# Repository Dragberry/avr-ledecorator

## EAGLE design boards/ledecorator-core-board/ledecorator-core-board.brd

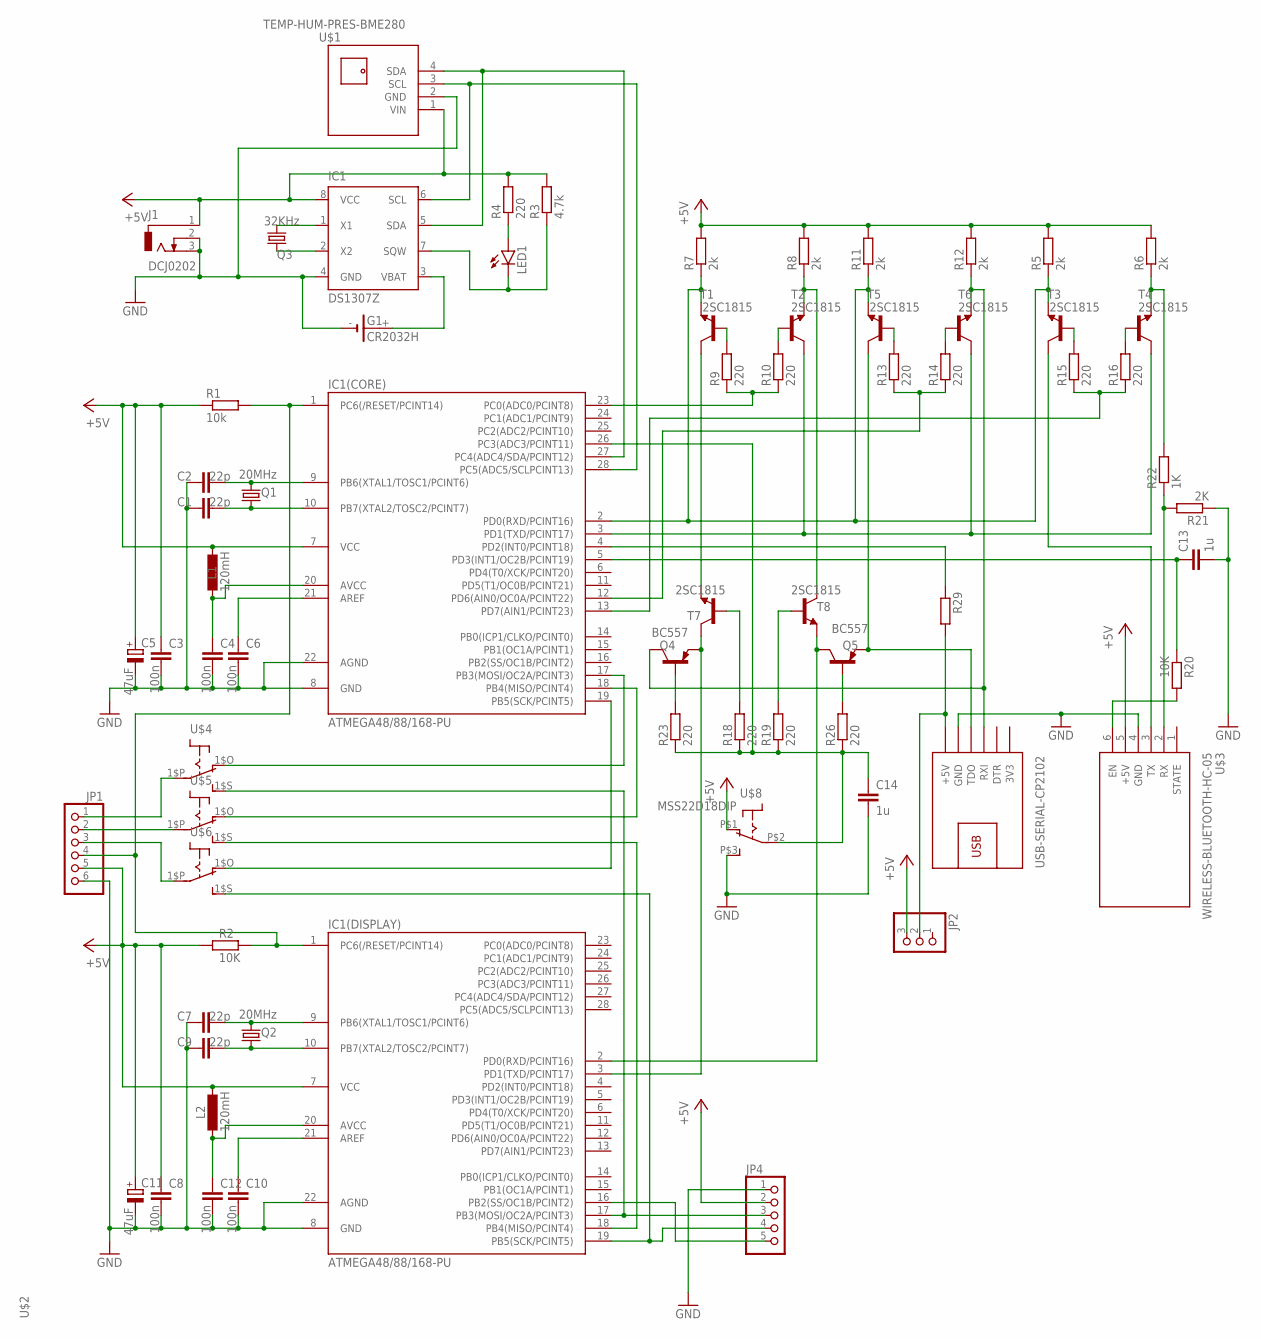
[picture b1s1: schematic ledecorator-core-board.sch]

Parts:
C1, C2, C7, C9: 22p; C025-025X050
C3, C8, C10, C12: 100n; C025-025X050
C4, C6: 100n; C1206
C5, C11: 47uF; E2-4
C13: 1u; C1206
C14: 1u; C050-025X075
G1: CR2032H
IC1: DS1307Z; SOIC8
IC1(CORE), IC1(DISPLAY): ATMEGA48/88/168-PU; DIL28-3
J1: DCJ0202
JP1: PINHD-1X6/90; 1X06/90
JP2: PINHD-1X3/90; 1X03/90
JP4: PINHD-1X5; 1X05
L1, L2: 120mH; 0207/10
LED1: LED3MM
Q1, Q2: 20MHz; HC49/S
Q3: 32KHz; TC26H
Q4, Q5: BC557; TO92-EBC
R1: 10k; 0207/10
R2, R20: 10K; 0207/10
R3: 4.7k; R1206
R4, R23, R26: 220; R1206
R5, R6, R11: 2k; 0207/12
R7, R8: 2k; R1206
R9, R10, R13, R14, R15, R16, R18, R19: 220; 0207/10
R12: 2k; 0207/10
R21: 2K; 0207/10
R22: 1K; 0207/10
R29: R-EU_0207/10; 0207/10
T1, T2, T3, T4, T5, T6, T7, T8: 2SC1815; TO92-ECB
U$1: TEMP-HUM-PRES-BME280
U$2: USB-SERIAL-CP2102
U$3: WIRELESS-BLUETOOTH-HC-05
U$4, U$5, U$6: SS12D00DIP; SS12D00
U$8: MSS22D18DIP; MSS22D18

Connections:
3V3: U$2.1 (3V3)
+5V: C3.1, C5.+, C8.1, C11.+, IC1.8 (VCC), IC1(CORE).7 (VCC), IC1(DISPLAY).7 (VCC), J1.1, JP1.5, JP2.3, JP4.2, L1.1, L2.1, R1.1, R2.1, R3.2, R4.2, R5.2, R6.2, R7.2, R8.2, R11.2, R12.2, U$1.1 (VIN), U$3.5 (+5V), U$8.P$1 (O)
BLE$CTRL: IC1(CORE).13 (PD7(AIN1/PCINT23)), R15.1, R16.1
BLE$RX: R21.2, R22.1, U$3.2 (RX)
BLE$TX: T3.C, U$3.3 (TX)
BLR$STATE$1: C13.1, IC1(CORE).5 (PD3(INT1/OC2B/PCINT19)), R20.1
DISPLAY$RX: IC1(DISPLAY).2 (PD0(RXD/PCINT16)), Q5.C, T8.E
DISPLAY$SRC: C14.1, IC1(CORE).26 (PC3(ADC3/PCINT11)), R18.1, R19.1, R23.1, R26.1, U$8.P$2
DISPLAY$TX: IC1(DISPLAY).3 (PD1(TXD/PCINT17)), Q4.E, T7.C
GND: C1.1, C2.1, C3.2, C4.2, C5.-, C6.2, C7.1, C8.2, C9.1, C10.2, C11.-, C12.2, C13.2, C14.2, G1.-, IC1.4 (GND), IC1(CORE).8 (GND), IC1(CORE).22 (AGND), IC1(DISPLAY).8 (GND), IC1(DISPLAY).22 (AGND), J1.2, J1.3, JP1.6, JP4.1, R21.1, U$1.2 (GND), U$2.5 (GND), U$3.4 (GND), U$8.P$3 (S)
MISO: JP1.2, U$5.1$P
MOSI: JP1.1, U$4.1$P
unnamed: C6.1, IC1(CORE).21 (AREF)
unnamed: Q4.B, R23.2
unnamed: C2.2, IC1(CORE).9 (PB6(XTAL1/TOSC1/PCINT6)), Q1.2
unnamed: C1.2, IC1(CORE).10 (PB7(XTAL2/TOSC2/PCINT7)), Q1.1
unnamed: IC1.2 (X2), Q3.2
unnamed: C4.1, IC1(CORE).20 (AVCC), L1.2
unnamed: C7.2, IC1(DISPLAY).9 (PB6(XTAL1/TOSC1/PCINT6)), Q2.2
unnamed: C9.2, IC1(DISPLAY).10 (PB7(XTAL2/TOSC2/PCINT7)), Q2.1
unnamed: C10.1, IC1(DISPLAY).21 (AREF)
unnamed: C12.1, IC1(DISPLAY).20 (AVCC), L2.2
unnamed: LED1.A, R4.1
unnamed: G1.+, IC1.3 (VBAT)
unnamed: IC1.1 (X1), Q3.1
unnamed: IC1.7 (SQW), LED1.K (C), R3.1
unnamed: R10.2, T2.B
unnamed: R9.2, T1.B
unnamed: IC1(CORE).23 (PC0(ADC0/PCINT8)), R9.1, R10.1
unnamed: R15.2, T3.B
unnamed: R16.2, T4.B
unnamed: R20.2, U$3.6 (EN)
unnamed: R13.2, T5.B
unnamed: R14.2, T6.B
unnamed: R18.2, T7.B
unnamed: R19.2, T8.B
unnamed: R6.1, R22.2, T4.E
unnamed: IC1(DISPLAY).16 (PB2(SS/OC1B/PCINT2)), JP4.5
unnamed: T1.C, T7.E
unnamed: R8.1, T2.E, T8.C
unnamed: IC1(CORE).18 (PB4(MISO/PCINT4)), U$5.1$O (O)
unnamed: IC1(CORE).17 (PB3(MOSI/OC2A/PCINT3)), U$4.1$O (O)
unnamed: Q5.B, R26.2
unnamed: JP2.2, R29.2, U$2.6 (+5V)
unnamed: IC1(DISPLAY).18 (PB4(MISO/PCINT4)), U$5.1$S (S)
unnamed: IC1(DISPLAY).17 (PB3(MOSI/OC2A/PCINT3)), JP4.3, U$4.1$S (S)
RESET: IC1(CORE).1 (PC6(/RESET/PCINT14)), IC1(DISPLAY).1 (PC6(/RESET/PCINT14)), JP1.4, R1.2, R2.2
RX: IC1(CORE).2 (PD0(RXD/PCINT16)), R5.1, R7.1, R11.1, T1.E, T3.E, T5.E
SCK: JP1.3, U$6.1$P
SCK$CORE: IC1(CORE).19 (PB5(SCK/PCINT5)), U$6.1$O (O)
SCK$DISPLAY: IC1(DISPLAY).19 (PB5(SCK/PCINT5)), JP4.4, U$6.1$S (S)
SCL: IC1.6 (SCL), IC1(CORE).28 (PC5(ADC5/SCLPCINT13)), U$1.3 (SCL)
SDA: IC1.5 (SDA), IC1(CORE).27 (PC4(ADC4/SDA/PCINT12)), U$1.4 (SDA)
TX: IC1(CORE).3 (PD1(TXD/PCINT17)), T2.C, T4.C, T6.C
USB$CTRL: IC1(CORE).12 (PD6(AIN0/OC0A/PCINT22)), R13.1, R14.1
USB$RX: Q4.C, R12.1, T6.E, U$2.3 (RXI)
USB$STATE: IC1(CORE).4 (PD2(INT0/PCINT18)), R29.1
USB$TX: Q5.E, T5.C, U$2.4 (TDO)

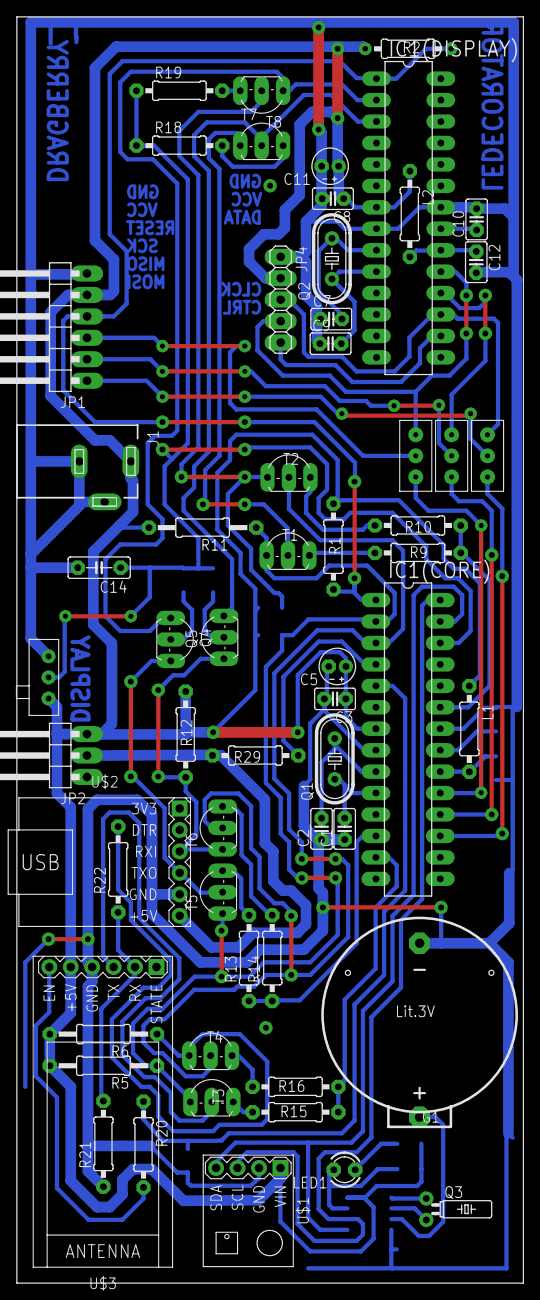
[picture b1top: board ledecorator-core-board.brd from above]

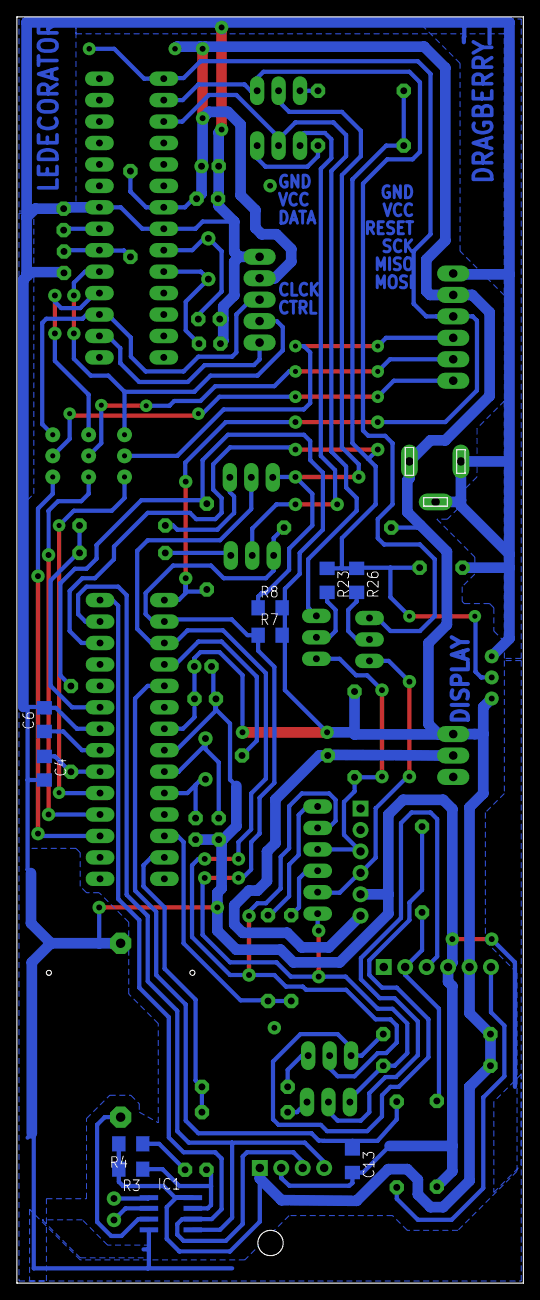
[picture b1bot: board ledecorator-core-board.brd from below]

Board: 2 copper layers, 60.0 x 150.0 mm, 69 parts (10 on the bottom side), 57 nets.

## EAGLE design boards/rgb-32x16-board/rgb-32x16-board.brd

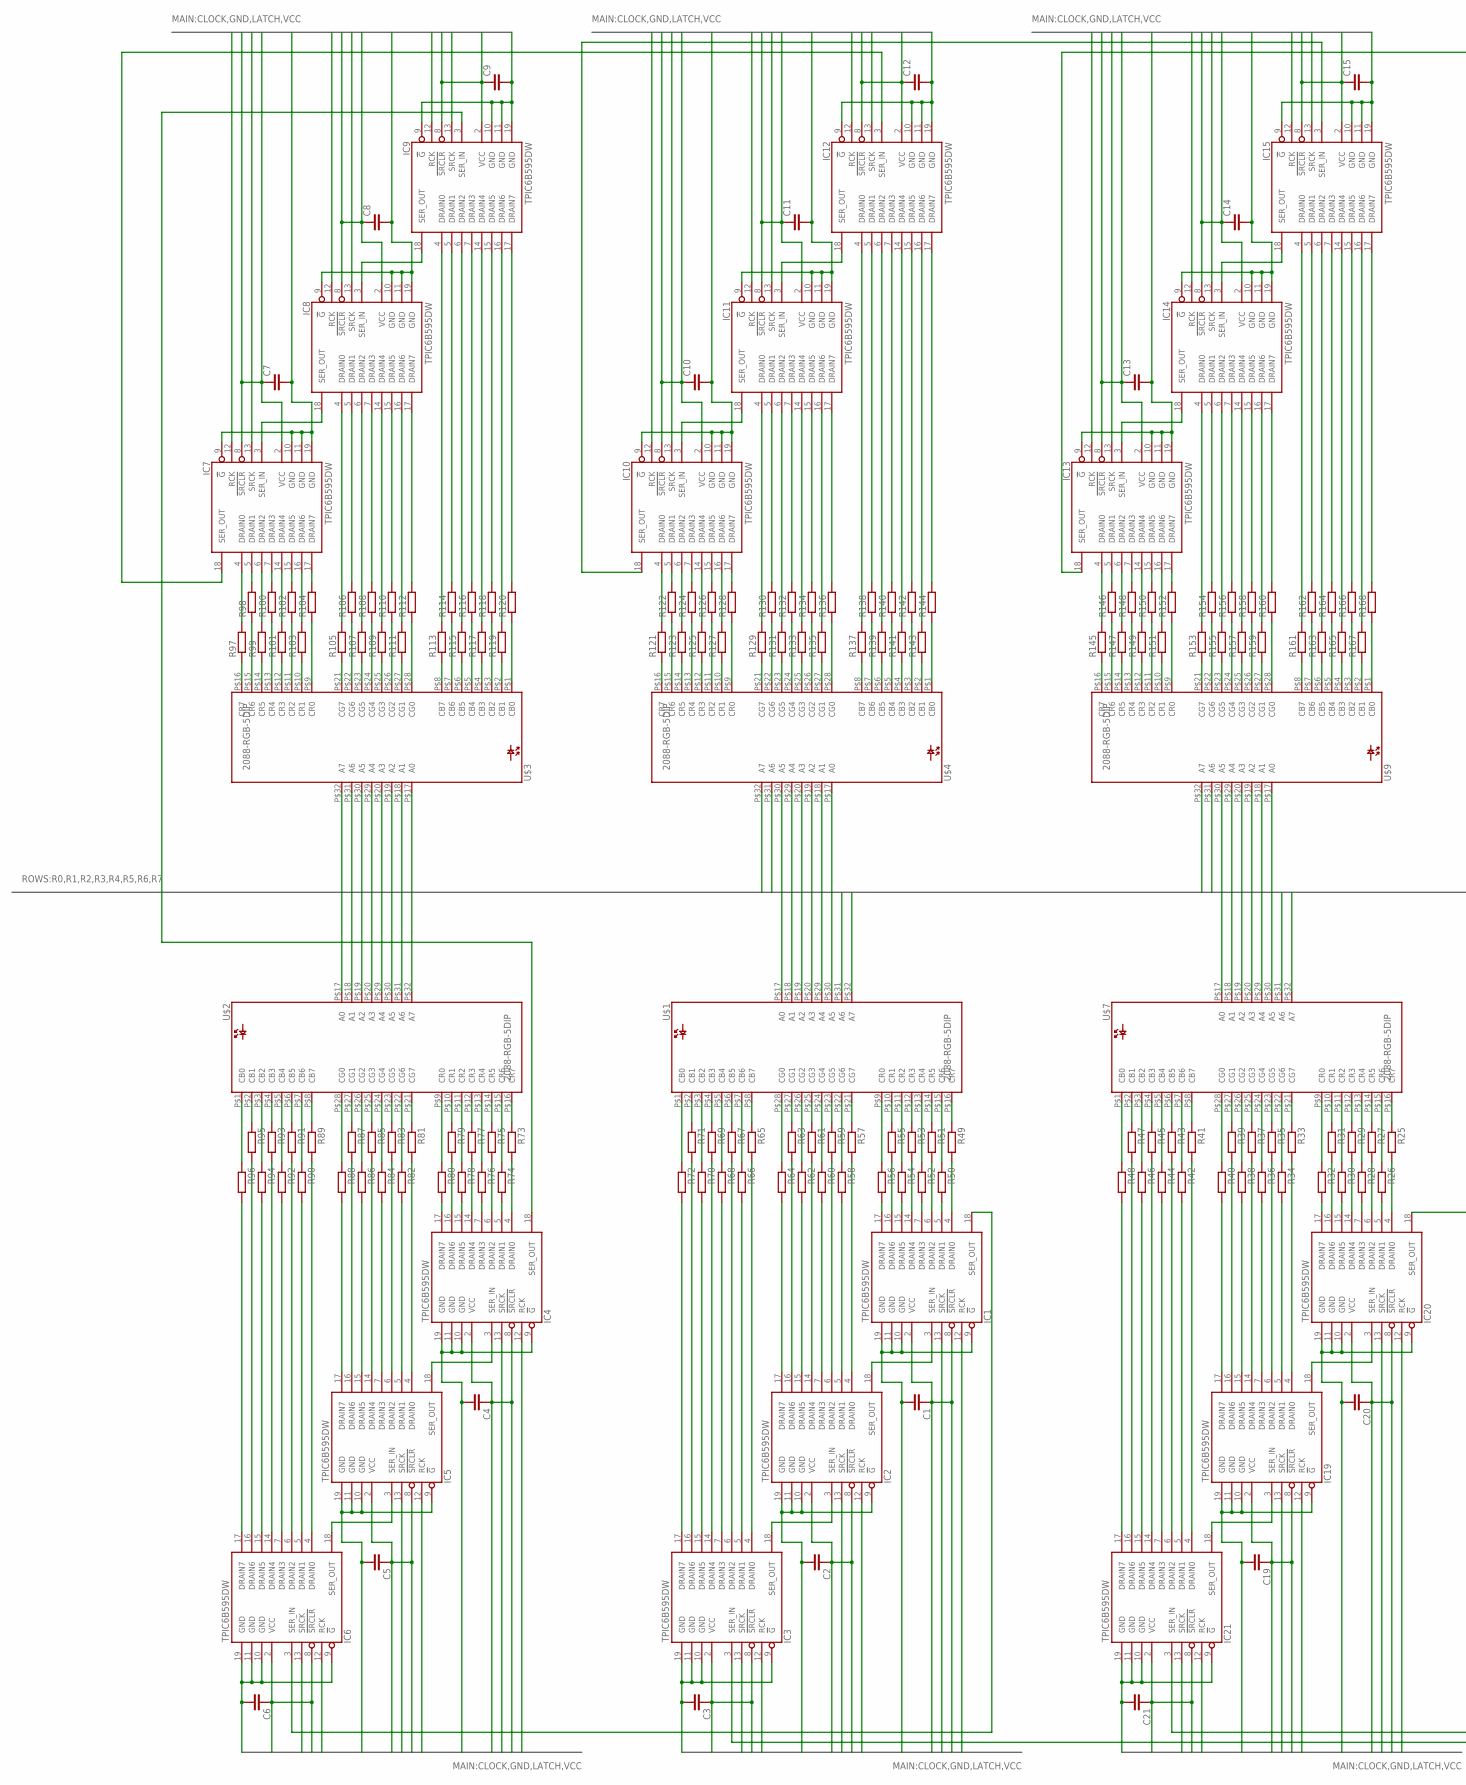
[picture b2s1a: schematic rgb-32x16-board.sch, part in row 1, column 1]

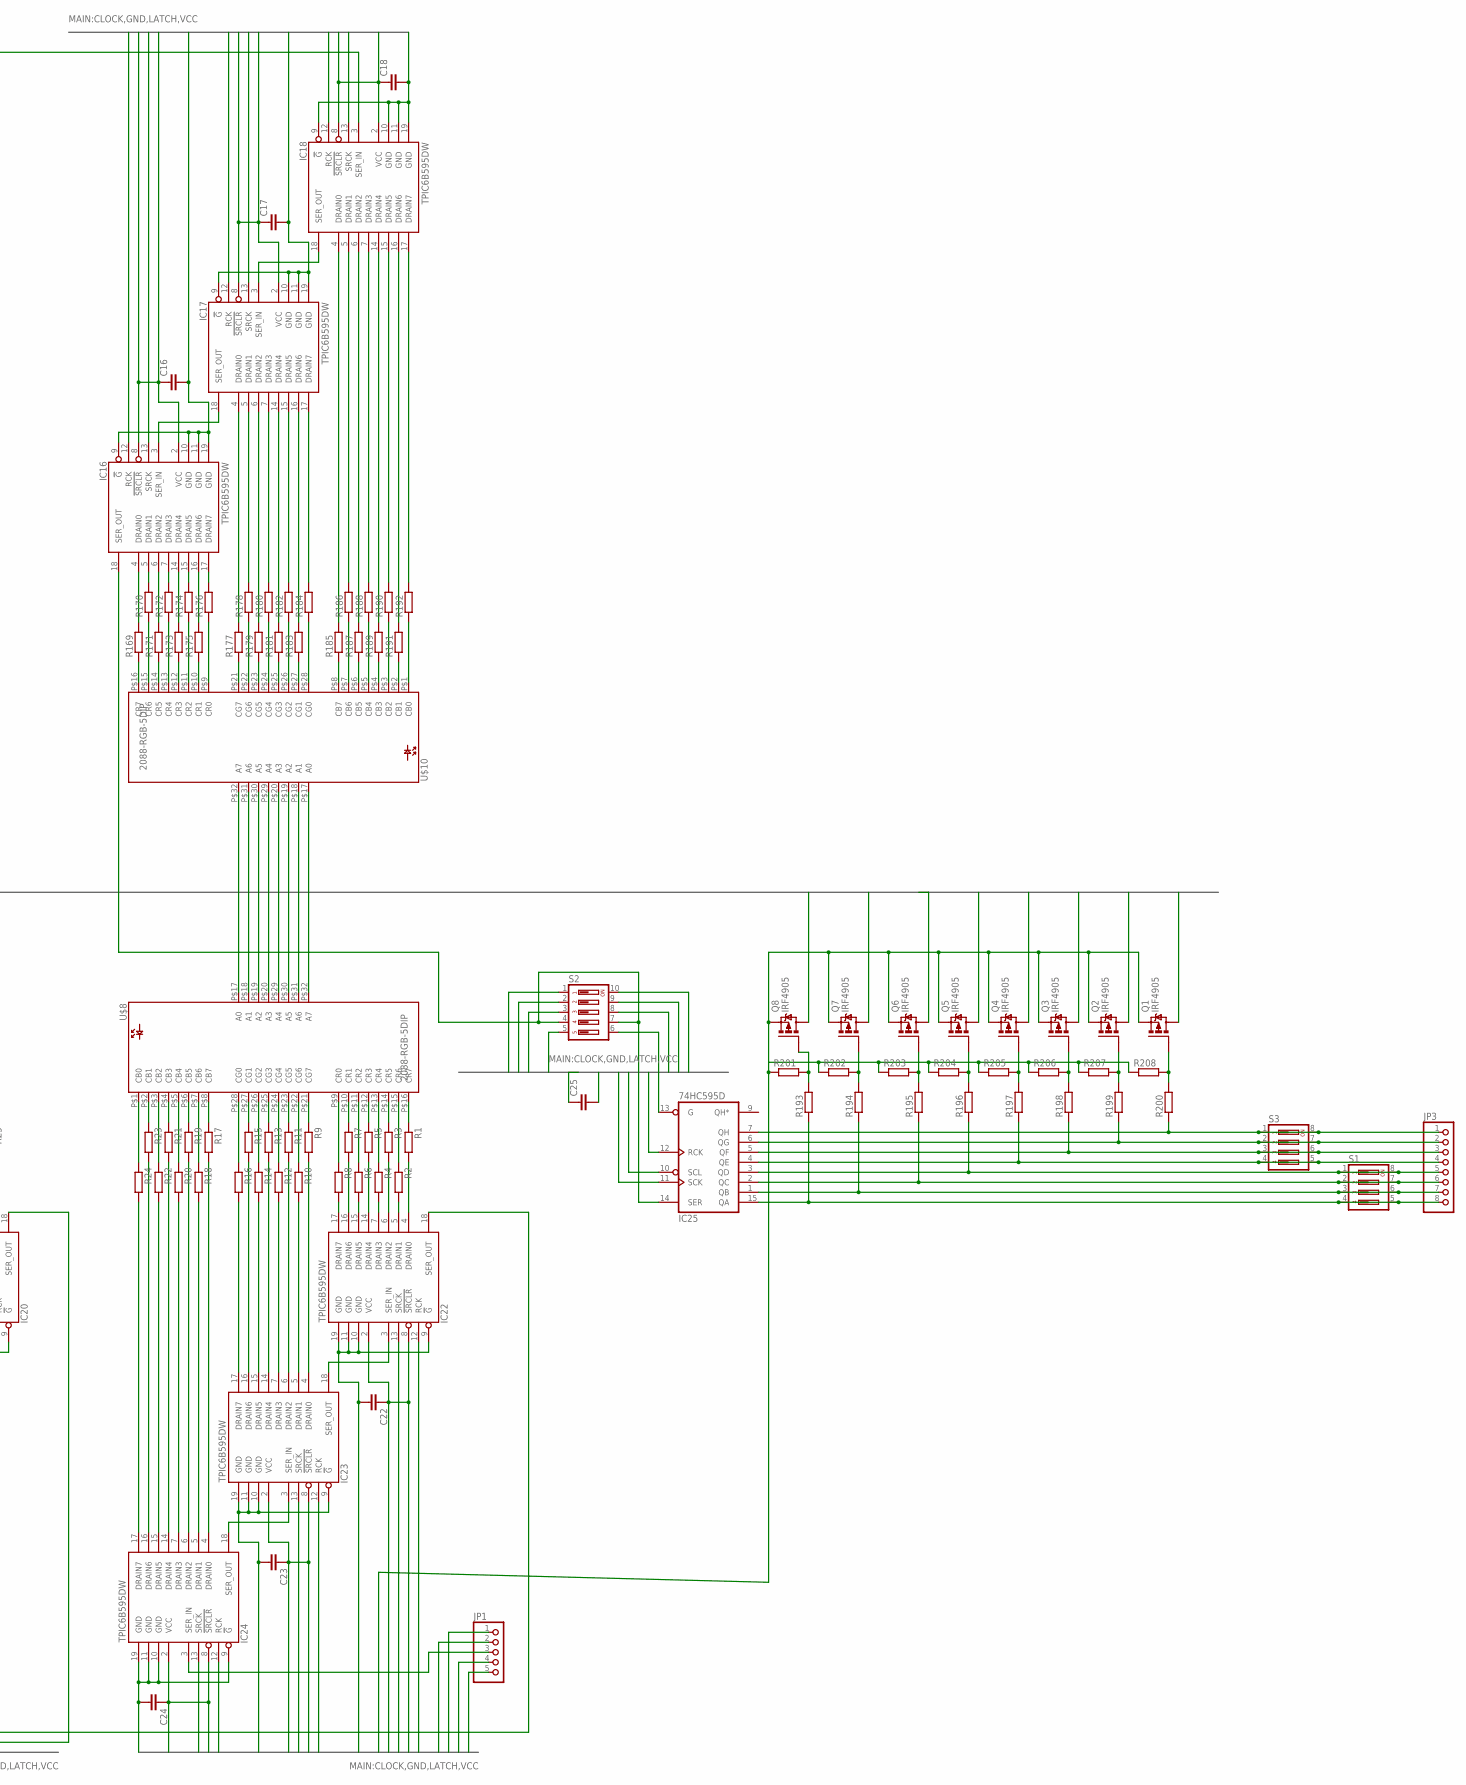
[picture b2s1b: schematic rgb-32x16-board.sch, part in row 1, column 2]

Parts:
C1, C2, C3, C4, C5, C6, C7, C8, C9, C10, C11, C12, C13, C14, C15, C16, C17, C18, C19, C20, C21, C22, C23, C24, C25: C-EUC1206; C1206
IC1, IC2, IC3, IC4, IC5, IC6, IC7, IC8, IC9, IC10, IC11, IC12, IC13, IC14, IC15, IC16, IC17, IC18, IC19, IC20, IC21, IC22, IC23, IC24: TPIC6B595DW; SO20W
IC25: 74HC595D; SO16
JP1: PINHD-1X5/90; 1X05/90
JP3: PINHD-1X8/90; 1X08/90
Q1, Q2, Q3, Q4, Q5, Q6, Q7, Q8: IRF4905; TO220BH
R1, R2, R3, R4, R5, R6, R7, R8, R9, R10, R11, R12, R13, R14, R15, R16, R17, R18, R19, R20, R21, R22, R23, R24, R25, R26, R27, R28, R29, R30, R31, R32, R33, R34, R35, R36, R37, R38, R39, R40, R41, R42, R43, R44, R45, R46, R47, R48, R49, R50, R51, R52, R53, R54, R55, R56, R57, R58, R59, R60, R61, R62, R63, R64, R65, R66, R67, R68, R69, R70, R71, R72, R73, R74, R75, R76, R77, R78, R79, R80, R81, R82, R83, R84, R85, R86, R87, R88, R89, R90, R91, R92, R93, R94, R95, R96, R97, R98, R99, R100, R101, R102, R103, R104, R105, R106, R107, R108, R109, R110, R111, R112, R113, R114, R115, R116, R117, R118, R119, R120, R121, R122, R123, R124, R125, R126, R127, R128, R129, R130, R131, R132, R133, R134, R135, R136, R137, R138, R139, R140, R141, R142, R143, R144, R145, R146, R147, R148, R149, R150, R151, R152, R153, R154, R155, R156, R157, R158, R159, R160, R161, R162, R163, R164, R165, R166, R167, R168, R169, R170, R171, R172, R173, R174, R175, R176, R177, R178, R179, R180, R181, R182, R183, R184, R185, R186, R187, R188, R189, R190, R191, R192, R201, R202, R203, R204, R205, R206, R207, R208: R-EU_R1206; R1206
R193, R194, R195, R196, R197, R198, R199, R200: R-EU_0207/10; 0207/10
S1, S3: DIP04YL
S2: DIP05YL
U$1, U$2, U$3, U$4, U$7, U$8, U$9, U$10: 2088-RGB-5DIP; 2088-RGB-5

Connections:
CLOCK: IC1.13 (SRCK), IC2.13 (SRCK), IC3.13 (SRCK), IC4.13 (SRCK), IC5.13 (SRCK), IC6.13 (SRCK), IC7.13 (SRCK), IC8.13 (SRCK), IC9.13 (SRCK), IC10.13 (SRCK), IC11.13 (SRCK), IC12.13 (SRCK), IC13.13 (SRCK), IC14.13 (SRCK), IC15.13 (SRCK), IC16.13 (SRCK), IC17.13 (SRCK), IC18.13 (SRCK), IC19.13 (SRCK), IC20.13 (SRCK), IC21.13 (SRCK), IC22.13 (SRCK), IC23.13 (SRCK), IC24.13 (SRCK), IC25.11 (SCK), JP1.2, S2.2, S2.9
GND: C1.2, C2.2, C3.2, C4.2, C5.2, C6.2, C7.2, C8.2, C9.2, C10.2, C11.2, C12.2, C13.2, C14.2, C15.2, C16.2, C17.2, C18.2, C19.2, C20.2, C21.2, C22.2, C23.2, C24.2, C25.2, IC1.9 (!G), IC1.10 (GND), IC1.11 (GND), IC1.19 (GND), IC2.9 (!G), IC2.10 (GND), IC2.11 (GND), IC2.19 (GND), IC3.9 (!G), IC3.10 (GND), IC3.11 (GND), IC3.19 (GND), IC4.9 (!G), IC4.10 (GND), IC4.11 (GND), IC4.19 (GND), IC5.9 (!G), IC5.10 (GND), IC5.11 (GND), IC5.19 (GND), IC6.9 (!G), IC6.10 (GND), IC6.11 (GND), IC6.19 (GND), IC7.9 (!G), IC7.10 (GND), IC7.11 (GND), IC7.19 (GND), IC8.9 (!G), IC8.10 (GND), IC8.11 (GND), IC8.19 (GND), IC9.9 (!G), IC9.10 (GND), IC9.11 (GND), IC9.19 (GND), IC10.9 (!G), IC10.10 (GND), IC10.11 (GND), IC10.19 (GND), IC11.9 (!G), IC11.10 (GND), IC11.11 (GND), IC11.19 (GND), IC12.9 (!G), IC12.10 (GND), IC12.11 (GND), IC12.19 (GND), IC13.9 (!G), IC13.10 (GND), IC13.11 (GND), IC13.19 (GND), IC14.9 (!G), IC14.10 (GND), IC14.11 (GND), IC14.19 (GND), IC15.9 (!G), IC15.10 (GND), IC15.11 (GND), IC15.19 (GND), IC16.9 (!G), IC16.10 (GND), IC16.11 (GND), IC16.19 (GND), IC17.9 (!G), IC17.10 (GND), IC17.11 (GND), IC17.19 (GND), IC18.9 (!G), IC18.10 (GND), IC18.11 (GND), IC18.19 (GND), IC19.9 (!G), IC19.10 (GND), IC19.11 (GND), IC19.19 (GND), IC20.9 (!G), IC20.10 (GND), IC20.11 (GND), IC20.19 (GND), IC21.9 (!G), IC21.10 (GND), IC21.11 (GND), IC21.19 (GND), IC22.9 (!G), IC22.10 (GND), IC22.11 (GND), IC22.19 (GND), IC23.9 (!G), IC23.10 (GND), IC23.11 (GND), IC23.19 (GND), IC24.9 (!G), IC24.10 (GND), IC24.11 (GND), IC24.19 (GND), IC25.8 (GND), IC25.13 (G), JP1.5, S2.1, S2.10
LATCH: IC1.12 (RCK), IC2.12 (RCK), IC3.12 (RCK), IC4.12 (RCK), IC5.12 (RCK), IC6.12 (RCK), IC7.12 (RCK), IC8.12 (RCK), IC9.12 (RCK), IC10.12 (RCK), IC11.12 (RCK), IC12.12 (RCK), IC13.12 (RCK), IC14.12 (RCK), IC15.12 (RCK), IC16.12 (RCK), IC17.12 (RCK), IC18.12 (RCK), IC19.12 (RCK), IC20.12 (RCK), IC21.12 (RCK), IC22.12 (RCK), IC23.12 (RCK), IC24.12 (RCK), IC25.12 (RCK), JP1.1, S2.3, S2.8
unnamed: R1.1, U$8.P$16 (CR7)
unnamed: R3.1, U$8.P$14 (CR5)
unnamed: R5.1, U$8.P$12 (CR3)
unnamed: R7.1, U$8.P$10 (CR1)
unnamed: R9.1, U$8.P$21 (CG7)
unnamed: R11.1, U$8.P$23 (CG5)
unnamed: R13.1, U$8.P$25 (CG3)
unnamed: R15.1, U$8.P$27 (CG1)
unnamed: IC22.17 (DRAIN7), R8.2
unnamed: IC22.16 (DRAIN6), R7.2
unnamed: IC22.15 (DRAIN5), R6.2
unnamed: IC22.14 (DRAIN4), R5.2
unnamed: IC22.7 (DRAIN3), R4.2
unnamed: IC22.6 (DRAIN2), R3.2
unnamed: IC22.5 (DRAIN1), R2.2
unnamed: IC22.4 (DRAIN0), R1.2
unnamed: IC23.4 (DRAIN0), R9.2
unnamed: IC23.5 (DRAIN1), R10.2
unnamed: IC23.6 (DRAIN2), R11.2
unnamed: IC23.7 (DRAIN3), R12.2
unnamed: IC23.14 (DRAIN4), R13.2
unnamed: IC23.15 (DRAIN5), R14.2
unnamed: IC23.16 (DRAIN6), R15.2
unnamed: IC23.17 (DRAIN7), R16.2
unnamed: IC24.4 (DRAIN0), R17.2
unnamed: IC24.5 (DRAIN1), R18.2
unnamed: IC24.6 (DRAIN2), R19.2
unnamed: IC24.7 (DRAIN3), R20.2
unnamed: IC24.14 (DRAIN4), R21.2
unnamed: IC24.15 (DRAIN5), R22.2
unnamed: IC24.16 (DRAIN6), R23.2
unnamed: IC24.17 (DRAIN7), R24.2
unnamed: R17.1, U$8.P$8 (CB7)
unnamed: R19.1, U$8.P$6 (CB5)
unnamed: R21.1, U$8.P$4 (CB3)
unnamed: R23.1, U$8.P$2 (CB1)
unnamed: R2.1, U$8.P$15 (CR6)
unnamed: R4.1, U$8.P$13 (CR4)
unnamed: R6.1, U$8.P$11 (CR2)
unnamed: R8.1, U$8.P$9 (CR0)
unnamed: R10.1, U$8.P$22 (CG6)
unnamed: R12.1, U$8.P$24 (CG4)
unnamed: R14.1, U$8.P$26 (CG2)
unnamed: R16.1, U$8.P$28 (CG0)
unnamed: R18.1, U$8.P$7 (CB6)
unnamed: R20.1, U$8.P$5 (CB4)
unnamed: R22.1, U$8.P$3 (CB2)
unnamed: R24.1, U$8.P$1 (CB0)
unnamed: IC21.3 (SER_IN), IC22.18 (SER_OUT)
unnamed: IC22.3 (SER_IN), IC23.18 (SER_OUT)
unnamed: IC20.17 (DRAIN7), R32.2
unnamed: IC23.3 (SER_IN), IC24.18 (SER_OUT)
unnamed: IC24.3 (SER_IN), JP1.3
unnamed: IC20.16 (DRAIN6), R31.2
unnamed: IC20.15 (DRAIN5), R30.2
unnamed: IC20.14 (DRAIN4), R29.2
unnamed: IC20.7 (DRAIN3), R28.2
unnamed: IC20.6 (DRAIN2), R27.2
unnamed: IC20.5 (DRAIN1), R26.2
unnamed: IC20.4 (DRAIN0), R25.2
unnamed: IC19.4 (DRAIN0), R33.2
unnamed: IC19.5 (DRAIN1), R34.2
unnamed: IC19.6 (DRAIN2), R35.2
unnamed: IC19.7 (DRAIN3), R36.2
unnamed: IC19.14 (DRAIN4), R37.2
unnamed: IC19.15 (DRAIN5), R38.2
unnamed: IC19.16 (DRAIN6), R39.2
unnamed: IC19.17 (DRAIN7), R40.2
unnamed: IC21.4 (DRAIN0), R41.2
unnamed: IC21.5 (DRAIN1), R42.2
unnamed: IC21.6 (DRAIN2), R43.2
unnamed: IC21.7 (DRAIN3), R44.2
unnamed: IC21.14 (DRAIN4), R45.2
unnamed: IC21.15 (DRAIN5), R46.2
unnamed: IC21.16 (DRAIN6), R47.2
unnamed: IC21.17 (DRAIN7), R48.2
unnamed: R25.1, U$7.P$16 (CR7)
unnamed: R27.1, U$7.P$14 (CR5)
unnamed: R29.1, U$7.P$12 (CR3)
unnamed: R31.1, U$7.P$10 (CR1)
unnamed: R33.1, U$7.P$21 (CG7)
unnamed: R35.1, U$7.P$23 (CG5)
unnamed: R37.1, U$7.P$25 (CG3)
unnamed: R39.1, U$7.P$27 (CG1)
unnamed: R41.1, U$7.P$8 (CB7)
unnamed: R43.1, U$7.P$6 (CB5)
unnamed: R45.1, U$7.P$4 (CB3)
unnamed: R47.1, U$7.P$2 (CB1)
unnamed: R26.1, U$7.P$15 (CR6)
unnamed: R28.1, U$7.P$13 (CR4)
unnamed: R30.1, U$7.P$11 (CR2)
unnamed: R32.1, U$7.P$9 (CR0)
unnamed: R34.1, U$7.P$22 (CG6)
unnamed: R36.1, U$7.P$24 (CG4)
unnamed: R38.1, U$7.P$26 (CG2)
unnamed: R40.1, U$7.P$28 (CG0)
unnamed: R42.1, U$7.P$7 (CB6)
unnamed: R44.1, U$7.P$5 (CB4)
unnamed: R46.1, U$7.P$3 (CB2)
unnamed: R48.1, U$7.P$1 (CB0)
unnamed: IC19.3 (SER_IN), IC21.18 (SER_OUT)
unnamed: IC19.18 (SER_OUT), IC20.3 (SER_IN)
unnamed: IC3.3 (SER_IN), IC20.18 (SER_OUT)
unnamed: IC1.17 (DRAIN7), R56.2
unnamed: IC1.16 (DRAIN6), R55.2
unnamed: IC1.15 (DRAIN5), R54.2
unnamed: IC1.14 (DRAIN4), R53.2
unnamed: IC1.7 (DRAIN3), R52.2
unnamed: IC1.6 (DRAIN2), R51.2
unnamed: IC1.5 (DRAIN1), R50.2
unnamed: IC1.4 (DRAIN0), R49.2
unnamed: IC2.4 (DRAIN0), R57.2
unnamed: IC2.5 (DRAIN1), R58.2
unnamed: IC2.6 (DRAIN2), R59.2
unnamed: IC2.7 (DRAIN3), R60.2
unnamed: IC2.14 (DRAIN4), R61.2
unnamed: IC2.15 (DRAIN5), R62.2
unnamed: IC2.16 (DRAIN6), R63.2
unnamed: IC2.17 (DRAIN7), R64.2
unnamed: IC3.4 (DRAIN0), R65.2
unnamed: IC3.5 (DRAIN1), R66.2
unnamed: IC3.6 (DRAIN2), R67.2
unnamed: IC3.7 (DRAIN3), R68.2
unnamed: IC3.14 (DRAIN4), R69.2
unnamed: IC3.15 (DRAIN5), R70.2
unnamed: IC3.16 (DRAIN6), R71.2
unnamed: IC3.17 (DRAIN7), R72.2
unnamed: IC1.18 (SER_OUT), IC6.3 (SER_IN)
unnamed: R49.1, U$1.P$16 (CR7)
unnamed: R51.1, U$1.P$14 (CR5)
unnamed: R53.1, U$1.P$12 (CR3)
unnamed: R55.1, U$1.P$10 (CR1)
unnamed: R57.1, U$1.P$21 (CG7)
unnamed: R59.1, U$1.P$23 (CG5)
unnamed: R61.1, U$1.P$25 (CG3)
unnamed: R63.1, U$1.P$27 (CG1)
unnamed: R65.1, U$1.P$8 (CB7)
unnamed: R67.1, U$1.P$6 (CB5)
unnamed: R69.1, U$1.P$4 (CB3)
unnamed: R71.1, U$1.P$2 (CB1)
unnamed: R50.1, U$1.P$15 (CR6)
unnamed: R52.1, U$1.P$13 (CR4)
unnamed: R54.1, U$1.P$11 (CR2)
unnamed: R56.1, U$1.P$9 (CR0)
unnamed: R58.1, U$1.P$22 (CG6)
unnamed: R60.1, U$1.P$24 (CG4)
unnamed: R62.1, U$1.P$26 (CG2)
unnamed: R64.1, U$1.P$28 (CG0)
unnamed: R66.1, U$1.P$7 (CB6)
unnamed: R68.1, U$1.P$5 (CB4)
unnamed: R70.1, U$1.P$3 (CB2)
unnamed: R72.1, U$1.P$1 (CB0)
unnamed: IC2.3 (SER_IN), IC3.18 (SER_OUT)
unnamed: IC4.17 (DRAIN7), R80.2
unnamed: IC1.3 (SER_IN), IC2.18 (SER_OUT)
unnamed: IC4.16 (DRAIN6), R79.2
unnamed: IC4.15 (DRAIN5), R78.2
unnamed: IC4.14 (DRAIN4), R77.2
unnamed: IC4.7 (DRAIN3), R76.2
unnamed: IC4.6 (DRAIN2), R75.2
unnamed: IC4.5 (DRAIN1), R74.2
unnamed: IC4.4 (DRAIN0), R73.2
unnamed: IC5.4 (DRAIN0), R81.2
unnamed: IC5.5 (DRAIN1), R82.2
unnamed: IC5.6 (DRAIN2), R83.2
unnamed: IC5.7 (DRAIN3), R84.2
unnamed: IC5.14 (DRAIN4), R85.2
unnamed: IC5.15 (DRAIN5), R86.2
unnamed: IC5.16 (DRAIN6), R87.2
unnamed: IC5.17 (DRAIN7), R88.2
unnamed: IC6.4 (DRAIN0), R89.2
unnamed: IC6.5 (DRAIN1), R90.2
unnamed: IC6.6 (DRAIN2), R91.2
unnamed: IC6.7 (DRAIN3), R92.2
unnamed: IC6.14 (DRAIN4), R93.2
unnamed: IC6.15 (DRAIN5), R94.2
unnamed: IC6.16 (DRAIN6), R95.2
unnamed: IC6.17 (DRAIN7), R96.2
unnamed: R73.1, U$2.P$16 (CR7)
unnamed: R75.1, U$2.P$14 (CR5)
unnamed: R77.1, U$2.P$12 (CR3)
unnamed: R79.1, U$2.P$10 (CR1)
unnamed: R81.1, U$2.P$21 (CG7)
unnamed: R83.1, U$2.P$23 (CG5)
unnamed: R85.1, U$2.P$25 (CG3)
unnamed: R87.1, U$2.P$27 (CG1)
unnamed: R89.1, U$2.P$8 (CB7)
unnamed: R91.1, U$2.P$6 (CB5)
unnamed: R93.1, U$2.P$4 (CB3)
unnamed: R95.1, U$2.P$2 (CB1)
unnamed: R74.1, U$2.P$15 (CR6)
unnamed: R76.1, U$2.P$13 (CR4)
unnamed: R78.1, U$2.P$11 (CR2)
unnamed: R80.1, U$2.P$9 (CR0)
unnamed: R82.1, U$2.P$22 (CG6)
unnamed: R84.1, U$2.P$24 (CG4)
unnamed: R86.1, U$2.P$26 (CG2)
unnamed: R88.1, U$2.P$28 (CG0)
unnamed: R90.1, U$2.P$7 (CB6)
unnamed: R92.1, U$2.P$5 (CB4)
unnamed: R94.1, U$2.P$3 (CB2)
unnamed: R96.1, U$2.P$1 (CB0)
unnamed: IC5.3 (SER_IN), IC6.18 (SER_OUT)
unnamed: IC4.3 (SER_IN), IC5.18 (SER_OUT)
unnamed: IC7.17 (DRAIN7), R104.2
unnamed: IC7.16 (DRAIN6), R103.2
unnamed: IC7.15 (DRAIN5), R102.2
unnamed: IC7.14 (DRAIN4), R101.2
unnamed: IC7.7 (DRAIN3), R100.2
unnamed: IC7.6 (DRAIN2), R99.2
unnamed: IC7.5 (DRAIN1), R98.2
unnamed: IC7.4 (DRAIN0), R97.2
unnamed: IC8.4 (DRAIN0), R105.2
unnamed: IC8.5 (DRAIN1), R106.2
unnamed: IC8.6 (DRAIN2), R107.2
unnamed: IC8.7 (DRAIN3), R108.2
unnamed: IC8.14 (DRAIN4), R109.2
unnamed: IC8.15 (DRAIN5), R110.2
unnamed: IC8.16 (DRAIN6), R111.2
unnamed: IC8.17 (DRAIN7), R112.2
unnamed: IC9.4 (DRAIN0), R113.2
unnamed: IC9.5 (DRAIN1), R114.2
unnamed: IC9.6 (DRAIN2), R115.2
unnamed: IC9.7 (DRAIN3), R116.2
unnamed: IC9.14 (DRAIN4), R117.2
unnamed: IC9.15 (DRAIN5), R118.2
unnamed: IC9.16 (DRAIN6), R119.2
unnamed: IC9.17 (DRAIN7), R120.2
unnamed: IC4.18 (SER_OUT), IC9.3 (SER_IN)
unnamed: R97.1, U$3.P$16 (CR7)
unnamed: R99.1, U$3.P$14 (CR5)
unnamed: R101.1, U$3.P$12 (CR3)
unnamed: R103.1, U$3.P$10 (CR1)
unnamed: R105.1, U$3.P$21 (CG7)
unnamed: R107.1, U$3.P$23 (CG5)
unnamed: R109.1, U$3.P$25 (CG3)
unnamed: R111.1, U$3.P$27 (CG1)
unnamed: R113.1, U$3.P$8 (CB7)
unnamed: R115.1, U$3.P$6 (CB5)
unnamed: R117.1, U$3.P$4 (CB3)
unnamed: R119.1, U$3.P$2 (CB1)
unnamed: R98.1, U$3.P$15 (CR6)
unnamed: R100.1, U$3.P$13 (CR4)
unnamed: R102.1, U$3.P$11 (CR2)
unnamed: R104.1, U$3.P$9 (CR0)
unnamed: R106.1, U$3.P$22 (CG6)
unnamed: R108.1, U$3.P$24 (CG4)
unnamed: R110.1, U$3.P$26 (CG2)
unnamed: R112.1, U$3.P$28 (CG0)
unnamed: R114.1, U$3.P$7 (CB6)
unnamed: R116.1, U$3.P$5 (CB4)
unnamed: R118.1, U$3.P$3 (CB2)
unnamed: R120.1, U$3.P$1 (CB0)
unnamed: IC10.17 (DRAIN7), R128.2
unnamed: IC10.16 (DRAIN6), R127.2
unnamed: IC10.15 (DRAIN5), R126.2
unnamed: IC10.14 (DRAIN4), R125.2
unnamed: IC10.7 (DRAIN3), R124.2
unnamed: IC10.6 (DRAIN2), R123.2
unnamed: IC10.5 (DRAIN1), R122.2
unnamed: IC10.4 (DRAIN0), R121.2
unnamed: IC11.4 (DRAIN0), R129.2
unnamed: IC11.5 (DRAIN1), R130.2
unnamed: IC11.6 (DRAIN2), R131.2
unnamed: IC11.7 (DRAIN3), R132.2
unnamed: IC11.14 (DRAIN4), R133.2
unnamed: IC11.15 (DRAIN5), R134.2
unnamed: IC11.16 (DRAIN6), R135.2
unnamed: IC11.17 (DRAIN7), R136.2
unnamed: IC12.4 (DRAIN0), R137.2
unnamed: IC12.5 (DRAIN1), R138.2
unnamed: IC12.6 (DRAIN2), R139.2
unnamed: IC12.7 (DRAIN3), R140.2
unnamed: IC12.14 (DRAIN4), R141.2
unnamed: IC12.15 (DRAIN5), R142.2
unnamed: IC12.16 (DRAIN6), R143.2
unnamed: IC12.17 (DRAIN7), R144.2
unnamed: IC7.18 (SER_OUT), IC12.3 (SER_IN)
unnamed: IC7.3 (SER_IN), IC8.18 (SER_OUT)
unnamed: IC8.3 (SER_IN), IC9.18 (SER_OUT)
unnamed: R121.1, U$4.P$16 (CR7)
unnamed: R123.1, U$4.P$14 (CR5)
unnamed: R125.1, U$4.P$12 (CR3)
unnamed: R127.1, U$4.P$10 (CR1)
unnamed: R129.1, U$4.P$21 (CG7)
unnamed: R131.1, U$4.P$23 (CG5)
unnamed: R133.1, U$4.P$25 (CG3)
unnamed: R135.1, U$4.P$27 (CG1)
unnamed: R137.1, U$4.P$8 (CB7)
unnamed: R139.1, U$4.P$6 (CB5)
unnamed: R141.1, U$4.P$4 (CB3)
unnamed: R143.1, U$4.P$2 (CB1)
unnamed: R122.1, U$4.P$15 (CR6)
unnamed: R124.1, U$4.P$13 (CR4)
unnamed: R126.1, U$4.P$11 (CR2)
unnamed: R128.1, U$4.P$9 (CR0)
unnamed: R130.1, U$4.P$22 (CG6)
unnamed: R132.1, U$4.P$24 (CG4)
unnamed: R134.1, U$4.P$26 (CG2)
unnamed: R136.1, U$4.P$28 (CG0)
unnamed: R138.1, U$4.P$7 (CB6)
unnamed: R140.1, U$4.P$5 (CB4)
unnamed: R142.1, U$4.P$3 (CB2)
unnamed: R144.1, U$4.P$1 (CB0)
unnamed: IC11.3 (SER_IN), IC12.18 (SER_OUT)
unnamed: IC10.18 (SER_OUT), IC15.3 (SER_IN)
unnamed: IC10.3 (SER_IN), IC11.18 (SER_OUT)
unnamed: IC13.17 (DRAIN7), R152.2
unnamed: IC13.16 (DRAIN6), R151.2
unnamed: IC13.15 (DRAIN5), R150.2
unnamed: IC13.14 (DRAIN4), R149.2
unnamed: IC13.7 (DRAIN3), R148.2
unnamed: IC13.6 (DRAIN2), R147.2
unnamed: IC13.5 (DRAIN1), R146.2
unnamed: IC13.4 (DRAIN0), R145.2
unnamed: IC14.4 (DRAIN0), R153.2
unnamed: IC14.5 (DRAIN1), R154.2
unnamed: IC14.6 (DRAIN2), R155.2
unnamed: IC14.7 (DRAIN3), R156.2
unnamed: IC14.14 (DRAIN4), R157.2
unnamed: IC14.15 (DRAIN5), R158.2
unnamed: IC14.16 (DRAIN6), R159.2
unnamed: IC14.17 (DRAIN7), R160.2
unnamed: IC15.4 (DRAIN0), R161.2
unnamed: IC15.5 (DRAIN1), R162.2
unnamed: IC15.6 (DRAIN2), R163.2
unnamed: IC15.7 (DRAIN3), R164.2
unnamed: IC15.14 (DRAIN4), R165.2
unnamed: IC15.15 (DRAIN5), R166.2
unnamed: IC15.16 (DRAIN6), R167.2
unnamed: IC15.17 (DRAIN7), R168.2
unnamed: R145.1, U$9.P$16 (CR7)
unnamed: R147.1, U$9.P$14 (CR5)
unnamed: R149.1, U$9.P$12 (CR3)
unnamed: R151.1, U$9.P$10 (CR1)
unnamed: R153.1, U$9.P$21 (CG7)
unnamed: R155.1, U$9.P$23 (CG5)
unnamed: R157.1, U$9.P$25 (CG3)
unnamed: R159.1, U$9.P$27 (CG1)
unnamed: R161.1, U$9.P$8 (CB7)
unnamed: R163.1, U$9.P$6 (CB5)
unnamed: R165.1, U$9.P$4 (CB3)
unnamed: R167.1, U$9.P$2 (CB1)
unnamed: R146.1, U$9.P$15 (CR6)
unnamed: R148.1, U$9.P$13 (CR4)
unnamed: R150.1, U$9.P$11 (CR2)
unnamed: R152.1, U$9.P$9 (CR0)
unnamed: R154.1, U$9.P$22 (CG6)
unnamed: R156.1, U$9.P$24 (CG4)
unnamed: R158.1, U$9.P$26 (CG2)
unnamed: R160.1, U$9.P$28 (CG0)
unnamed: R162.1, U$9.P$7 (CB6)
unnamed: R164.1, U$9.P$5 (CB4)
unnamed: R166.1, U$9.P$3 (CB2)
unnamed: R168.1, U$9.P$1 (CB0)
unnamed: IC14.3 (SER_IN), IC15.18 (SER_OUT)
unnamed: IC13.3 (SER_IN), IC14.18 (SER_OUT)
unnamed: IC16.17 (DRAIN7), R176.2
unnamed: IC16.16 (DRAIN6), R175.2
unnamed: IC16.15 (DRAIN5), R174.2
unnamed: IC16.14 (DRAIN4), R173.2
unnamed: IC16.7 (DRAIN3), R172.2
unnamed: IC16.6 (DRAIN2), R171.2
unnamed: IC16.5 (DRAIN1), R170.2
unnamed: IC16.4 (DRAIN0), R169.2
unnamed: IC17.4 (DRAIN0), R177.2
unnamed: IC17.5 (DRAIN1), R178.2
unnamed: IC17.6 (DRAIN2), R179.2
unnamed: IC17.7 (DRAIN3), R180.2
unnamed: IC17.14 (DRAIN4), R181.2
unnamed: IC17.15 (DRAIN5), R182.2
unnamed: IC17.16 (DRAIN6), R183.2
unnamed: IC17.17 (DRAIN7), R184.2
unnamed: IC18.4 (DRAIN0), R185.2
unnamed: IC18.5 (DRAIN1), R186.2
unnamed: IC18.6 (DRAIN2), R187.2
unnamed: IC18.7 (DRAIN3), R188.2
unnamed: IC18.14 (DRAIN4), R189.2
unnamed: IC18.15 (DRAIN5), R190.2
unnamed: IC18.16 (DRAIN6), R191.2
unnamed: IC18.17 (DRAIN7), R192.2
unnamed: R169.1, U$10.P$16 (CR7)
unnamed: R171.1, U$10.P$14 (CR5)
unnamed: R173.1, U$10.P$12 (CR3)
unnamed: R175.1, U$10.P$10 (CR1)
unnamed: R177.1, U$10.P$21 (CG7)
unnamed: R179.1, U$10.P$23 (CG5)
unnamed: R181.1, U$10.P$25 (CG3)
unnamed: R183.1, U$10.P$27 (CG1)
unnamed: R185.1, U$10.P$8 (CB7)
unnamed: R187.1, U$10.P$6 (CB5)
unnamed: R189.1, U$10.P$4 (CB3)
unnamed: R191.1, U$10.P$2 (CB1)
unnamed: R170.1, U$10.P$15 (CR6)
unnamed: R172.1, U$10.P$13 (CR4)
unnamed: R174.1, U$10.P$11 (CR2)
unnamed: R176.1, U$10.P$9 (CR0)
unnamed: R178.1, U$10.P$22 (CG6)
unnamed: R180.1, U$10.P$24 (CG4)
unnamed: R182.1, U$10.P$26 (CG2)
unnamed: R184.1, U$10.P$28 (CG0)
unnamed: R186.1, U$10.P$7 (CB6)
unnamed: R188.1, U$10.P$5 (CB4)
unnamed: R190.1, U$10.P$3 (CB2)
unnamed: R192.1, U$10.P$1 (CB0)
unnamed: IC17.3 (SER_IN), IC18.18 (SER_OUT)
unnamed: IC16.3 (SER_IN), IC17.18 (SER_OUT)
unnamed: IC13.18 (SER_OUT), IC18.3 (SER_IN)
unnamed: Q8.G, R193.2, R201.2
unnamed: Q7.G, R194.2, R202.2
unnamed: Q6.G, R195.2, R203.2
unnamed: Q5.G, R196.2, R204.2
unnamed: Q4.G, R197.2, R205.2
unnamed: Q3.G, R198.2, R206.2
unnamed: Q2.G, R199.2, R207.2
unnamed: Q1.G, R200.2, R208.2
unnamed: IC25.15 (QA), JP3.8, R193.1, S1.4, S1.5
unnamed: IC25.1 (QB), JP3.7, R194.1, S1.3, S1.6
unnamed: IC25.3 (QD), JP3.5, R196.1, S1.1, S1.8
unnamed: IC25.4 (QE), JP3.4, R197.1, S3.4, S3.5
unnamed: IC25.5 (QF), JP3.3, R198.1, S3.3, S3.6
unnamed: IC25.7 (QH), JP3.1, R200.1, S3.1, S3.8
unnamed: IC16.18 (SER_OUT), IC25.14 (SER), S2.4, S2.7
unnamed: IC25.6 (QG), JP3.2, R199.1, S3.2, S3.7
unnamed: IC25.2 (QC), JP3.6, R195.1, S1.2, S1.7
R0: Q8.D, U$1.P$17 (A0), U$2.P$17 (A0), U$3.P$32 (A7), U$4.P$32 (A7), U$7.P$17 (A0), U$8.P$17 (A0), U$9.P$32 (A7), U$10.P$32 (A7)
R1: Q7.D, U$1.P$18 (A1), U$2.P$18 (A1), U$3.P$31 (A6), U$4.P$31 (A6), U$7.P$18 (A1), U$8.P$18 (A1), U$9.P$31 (A6), U$10.P$31 (A6)
R2: Q6.D, U$1.P$19 (A2), U$2.P$19 (A2), U$3.P$30 (A5), U$4.P$30 (A5), U$7.P$19 (A2), U$8.P$19 (A2), U$9.P$30 (A5), U$10.P$30 (A5)
R3: Q5.D, U$1.P$20 (A3), U$2.P$20 (A3), U$3.P$29 (A4), U$4.P$29 (A4), U$7.P$20 (A3), U$8.P$20 (A3), U$9.P$29 (A4), U$10.P$29 (A4)
R4: Q4.D, U$1.P$29 (A4), U$2.P$29 (A4), U$3.P$20 (A3), U$4.P$20 (A3), U$7.P$29 (A4), U$8.P$29 (A4), U$9.P$20 (A3), U$10.P$20 (A3)
R5: Q3.D, U$1.P$30 (A5), U$2.P$30 (A5), U$3.P$19 (A2), U$4.P$19 (A2), U$7.P$30 (A5), U$8.P$30 (A5), U$9.P$19 (A2), U$10.P$19 (A2)
R6: Q2.D, U$1.P$31 (A6), U$2.P$31 (A6), U$3.P$18 (A1), U$4.P$18 (A1), U$7.P$31 (A6), U$8.P$31 (A6), U$9.P$18 (A1), U$10.P$18 (A1)
R7: Q1.D, U$1.P$32 (A7), U$2.P$32 (A7), U$3.P$17 (A0), U$4.P$17 (A0), U$7.P$32 (A7), U$8.P$32 (A7), U$9.P$17 (A0), U$10.P$17 (A0)
VCC: C1.1, C2.1, C3.1, C4.1, C5.1, C6.1, C7.1, C8.1, C9.1, C10.1, C11.1, C12.1, C13.1, C14.1, C15.1, C16.1, C17.1, C18.1, C19.1, C20.1, C21.1, C22.1, C23.1, C24.1, C25.1, IC1.2 (VCC), IC1.8 (!SRCLR), IC2.2 (VCC), IC2.8 (!SRCLR), IC3.2 (VCC), IC3.8 (!SRCLR), IC4.2 (VCC), IC4.8 (!SRCLR), IC5.2 (VCC), IC5.8 (!SRCLR), IC6.2 (VCC), IC6.8 (!SRCLR), IC7.2 (VCC), IC7.8 (!SRCLR), IC8.2 (VCC), IC8.8 (!SRCLR), IC9.2 (VCC), IC9.8 (!SRCLR), IC10.2 (VCC), IC10.8 (!SRCLR), IC11.2 (VCC), IC11.8 (!SRCLR), IC12.2 (VCC), IC12.8 (!SRCLR), IC13.2 (VCC), IC13.8 (!SRCLR), IC14.2 (VCC), IC14.8 (!SRCLR), IC15.2 (VCC), IC15.8 (!SRCLR), IC16.2 (VCC), IC16.8 (!SRCLR), IC17.2 (VCC), IC17.8 (!SRCLR), IC18.2 (VCC), IC18.8 (!SRCLR), IC19.2 (VCC), IC19.8 (!SRCLR), IC20.2 (VCC), IC20.8 (!SRCLR), IC21.2 (VCC), IC21.8 (!SRCLR), IC22.2 (VCC), IC22.8 (!SRCLR), IC23.2 (VCC), IC23.8 (!SRCLR), IC24.2 (VCC), IC24.8 (!SRCLR), IC25.10 (SCL), IC25.16 (VCC), JP1.4, Q1.S, Q2.S, Q3.S, Q4.S, Q5.S, Q6.S, Q7.S, Q8.S, R201.1, R202.1, R203.1, R204.1, R205.1, R206.1, R207.1, R208.1, S2.5, S2.6

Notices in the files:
parts and their libraries:
diy-modules: Released under the Creative Commons Attribution 4.0 International License: http://creativecommons.org/licenses/by/4.0
